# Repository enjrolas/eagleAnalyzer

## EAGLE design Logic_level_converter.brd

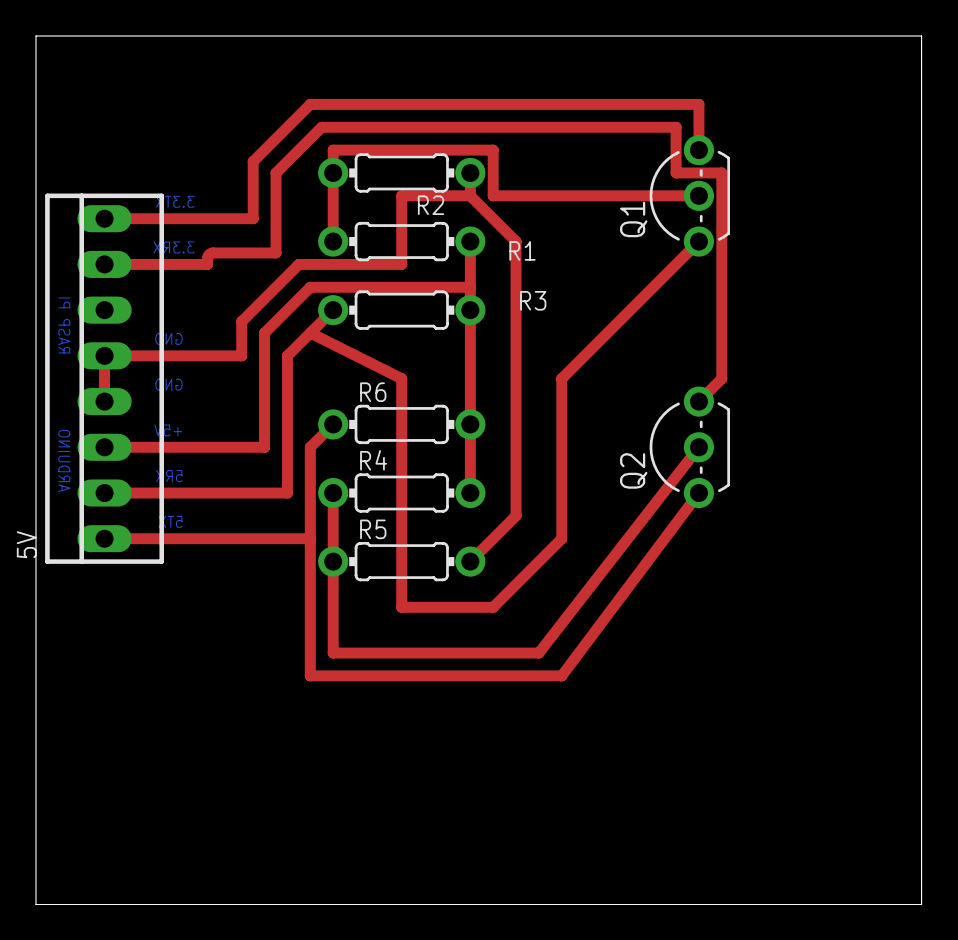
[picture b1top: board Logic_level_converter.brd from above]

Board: 2 copper layers, 49.2 x 48.2 mm, 9 parts (0 on the bottom side), 8 nets.

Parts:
5V: 22-23-2081
Q1, Q2: 2N7000; TO92-
R1, R4: 4.7k; 0204/7
R2, R3, R5, R6: 10k; 0204/7

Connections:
unnamed: 5V.4, 5V.5, R2.1, R5.2
S$1: Q1.2, R1.2, R2.2
S$2: 5V.8, Q1.3
S$3: 5V.2, Q1.1, R3.1
S$5: Q2.2, R4.1, R5.1
S$6: 5V.3, R1.1, R3.2, R4.2, R6.2
S$7: 5V.1, Q2.1, R6.1
S$8: 5V.7, Q2.3

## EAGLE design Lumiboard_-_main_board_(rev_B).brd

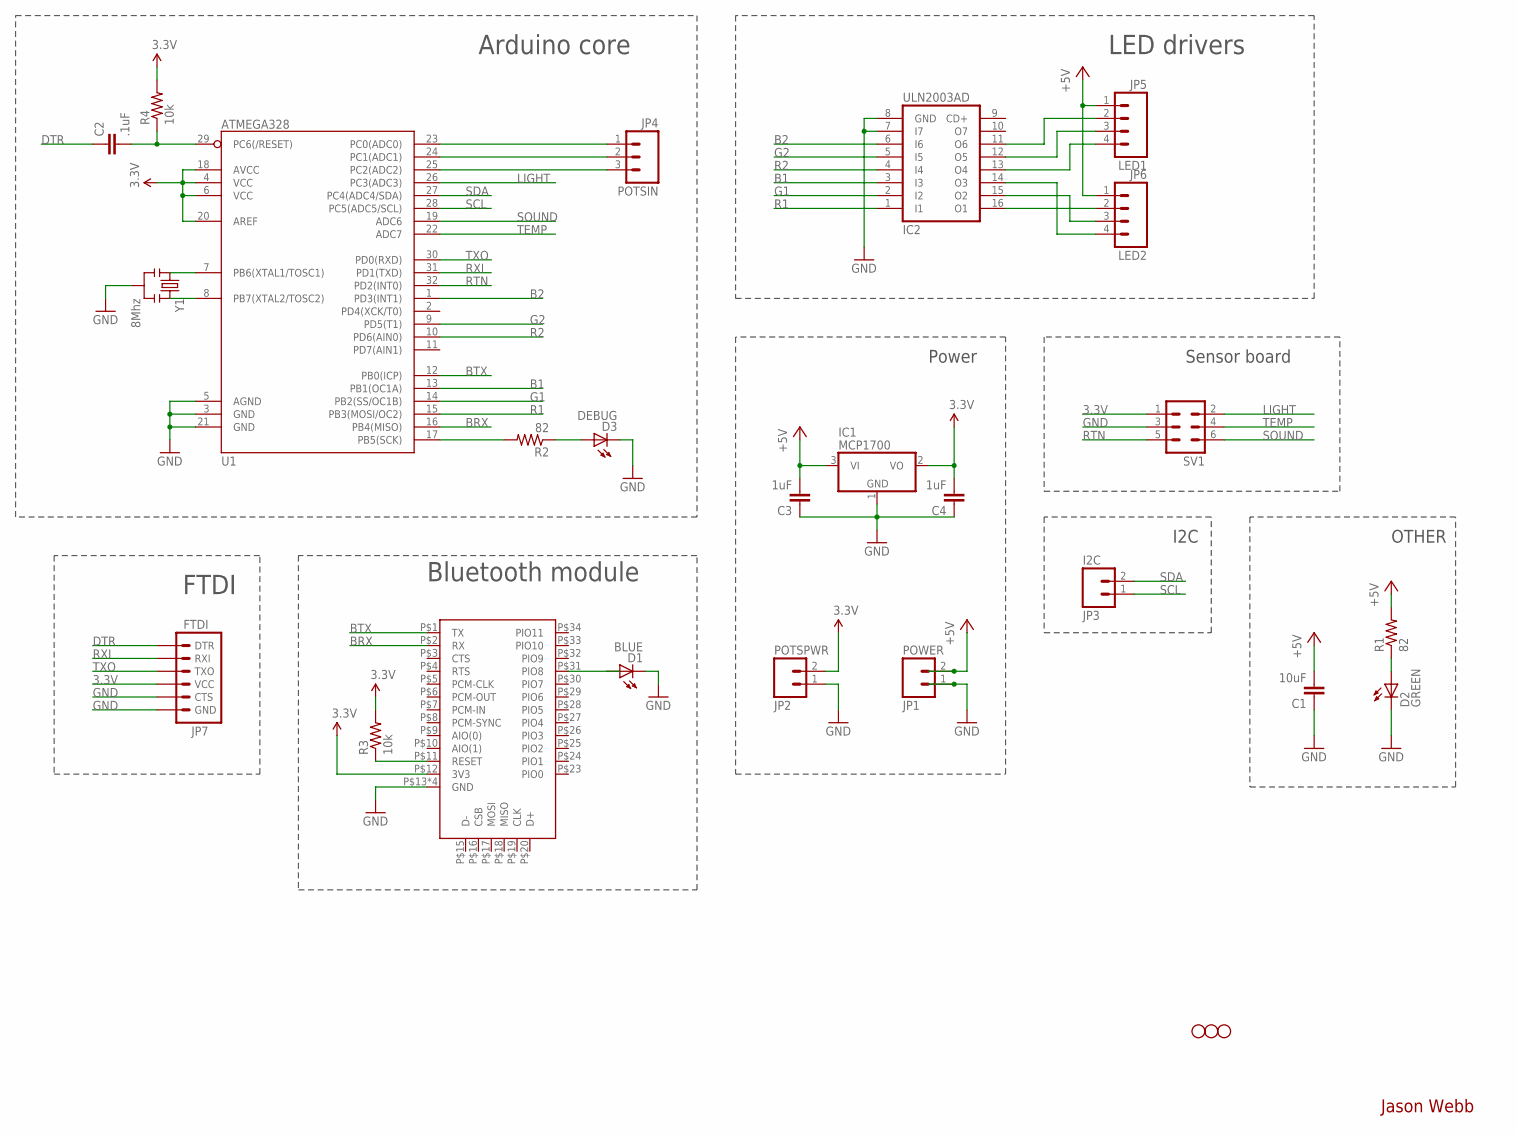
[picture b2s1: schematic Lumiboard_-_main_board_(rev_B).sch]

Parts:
C1: 10uF; 0805
C2: .1uF; 0805
C3, C4: 1uF; 0805
D1: BLUE; CHIPLED_0805
D2: GREEN; CHIPLED_0805
D3: DEBUG; CHIPLED_0805
I2C: JP3; 1X02
IC1: MCP1700; SOT23
IC2: ULN2003AD; SO16
JP2, JP4, JP5: STAND-OFFTIGHT; STAND-OFF-TIGHT
JP7: FTDI; 1X06_LOCK
LED1: JP5; 1X04
LED2: JP6; 1X04
POTSIN: JP4; 1X03
POTSPWR: JP2; 1X02
POWER: JP1; 1X02
R1, R2: 82; R0805
R3, R4: 10k; R0805
SV1: ML6
U1: ATMEGA328; TQFP32-08
U2: DX_BT_MODULE; DXBLUETOOTHMODULE
Y1: 8Mhz; RESONATOR-SMD

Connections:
3.3V: C4.2, IC1.2 (VO), JP7.4 (VCC), POTSPWR.2, R3.2, R4.2, SV1.1, U1.4 (VCC), U1.6 (VCC), U1.18 (AVCC), U1.20 (AREF), U2.P$12 (3V3)
+5V: C1.2, C3.2, IC1.3 (VI), LED1.1, LED2.1, POWER.2, R1.2
B1: IC2.3 (I3), U1.13 (PB1(OC1A))
B2: IC2.6 (I6), U1.1 (PD3(INT1))
BRX: U1.16 (PB4(MISO)), U2.P$2 (RX)
BTX: U1.12 (PB0(ICP)), U2.P$1 (TX)
DTR: C2.1, JP7.1 (DTR)
G1: IC2.2 (I2), U1.14 (PB2(SS/OC1B))
G2: IC2.5 (I5), U1.9 (PD5(T1))
GND: C1.1, C3.1, C4.1, D1.C, D2.C, D3.C, IC1.1 (GND), IC2.7 (I7), IC2.8 (GND), JP7.5 (CTS), JP7.6 (GND), POTSPWR.1, POWER.1, SV1.3, U1.3 (GND), U1.5 (AGND), U1.21 (GND), U2.P$13 (GND), U2.P$14 (GND), U2.P$21 (GND), U2.P$22 (GND), Y1.2
LIGHT: SV1.2, U1.26 (PC3(ADC3))
unnamed: IC2.16 (O1), LED2.2
unnamed: D1.A, U2.P$31 (PIO8)
unnamed: IC2.15 (O2), LED2.3
unnamed: R2.2, U1.17 (PB5(SCK))
unnamed: IC2.14 (O3), LED2.4
unnamed: U1.7 (PB6(XTAL1/TOSC1)), Y1.1
unnamed: U1.8 (PB7(XTAL2/TOSC2)), Y1.3
unnamed: D2.A, R1.1
unnamed: C2.2, R4.1, U1.29 (PC6(/RESET))
unnamed: R3.1, U2.P$11 (RESET)
unnamed: POTSIN.3, U1.25 (PC2(ADC2))
unnamed: D3.A, R2.1
unnamed: IC2.13 (O4), LED1.4
unnamed: IC2.12 (O5), LED1.3
unnamed: IC2.11 (O6), LED1.2
unnamed: POTSIN.2, U1.24 (PC1(ADC1))
unnamed: POTSIN.1, U1.23 (PC0(ADC0))
R1: IC2.1 (I1), U1.15 (PB3(MOSI/OC2))
R2: IC2.4 (I4), U1.10 (PD6(AIN0))
RTN: SV1.5, U1.32 (PD2(INT0))
RXI: JP7.2 (RXI), U1.31 (PD1(TXD))
SCL: I2C.1, U1.28 (PC5(ADC5/SCL))
SDA: I2C.2, U1.27 (PC4(ADC4/SDA))
SOUND: SV1.6, U1.19 (ADC6)
TEMP: SV1.4, U1.22 (ADC7)
TXO: JP7.3 (TXO), U1.30 (PD0(RXD))

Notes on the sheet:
Jason Webb
Arduino core
Bluetooth module
Sensor board
LED drivers
Power
FTDI
I2C
OTHER

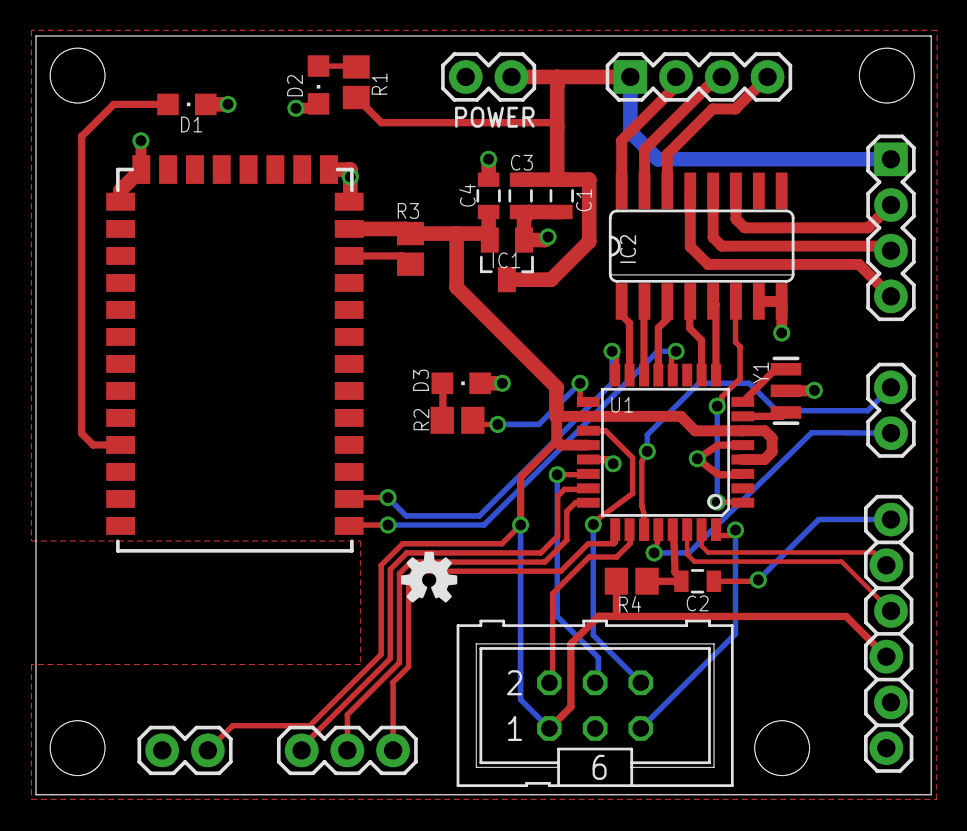
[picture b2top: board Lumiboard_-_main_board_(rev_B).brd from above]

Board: 2 copper layers, 49.7 x 42.2 mm, 29 parts (0 on the bottom side), 37 nets.

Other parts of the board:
JP3: STAND-OFFTIGHT; STAND-OFF-TIGHT
U$1: OSHW-LOGO-S

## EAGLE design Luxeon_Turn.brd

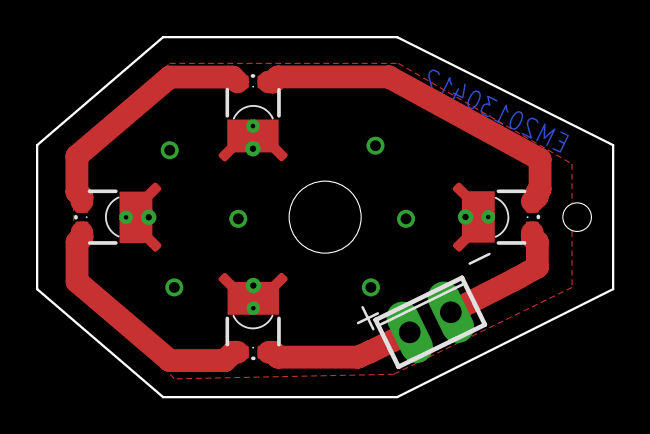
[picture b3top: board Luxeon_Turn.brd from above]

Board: 2 copper layers, 32.0 x 20.0 mm, 5 parts (0 on the bottom side), 6 nets.

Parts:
LED1, LED2, LED3, LED4: LUXEON_REBEL
X1: 2POL254

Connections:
unnamed: LED1.A, LED1.A@1, LED2.C, LED2.C@1
unnamed: LED2.A, LED2.A@1, LED3.C, LED3.C@1
unnamed: LED3.A, LED3.A@1, LED4.C, LED4.C@1
THERMAL: LED1.TH, LED1.TH@1, LED1.TH@2, LED1.TH@3, LED1.TH@4, LED2.TH, LED2.TH@1, LED2.TH@2, LED2.TH@3, LED2.TH@4, LED3.TH, LED3.TH@1, LED3.TH@2, LED3.TH@3, LED3.TH@4, LED4.TH, LED4.TH@1, LED4.TH@2, LED4.TH@3, LED4.TH@4
V+: LED4.A, LED4.A@1, X1.1
V-: LED1.C, LED1.C@1, X1.2

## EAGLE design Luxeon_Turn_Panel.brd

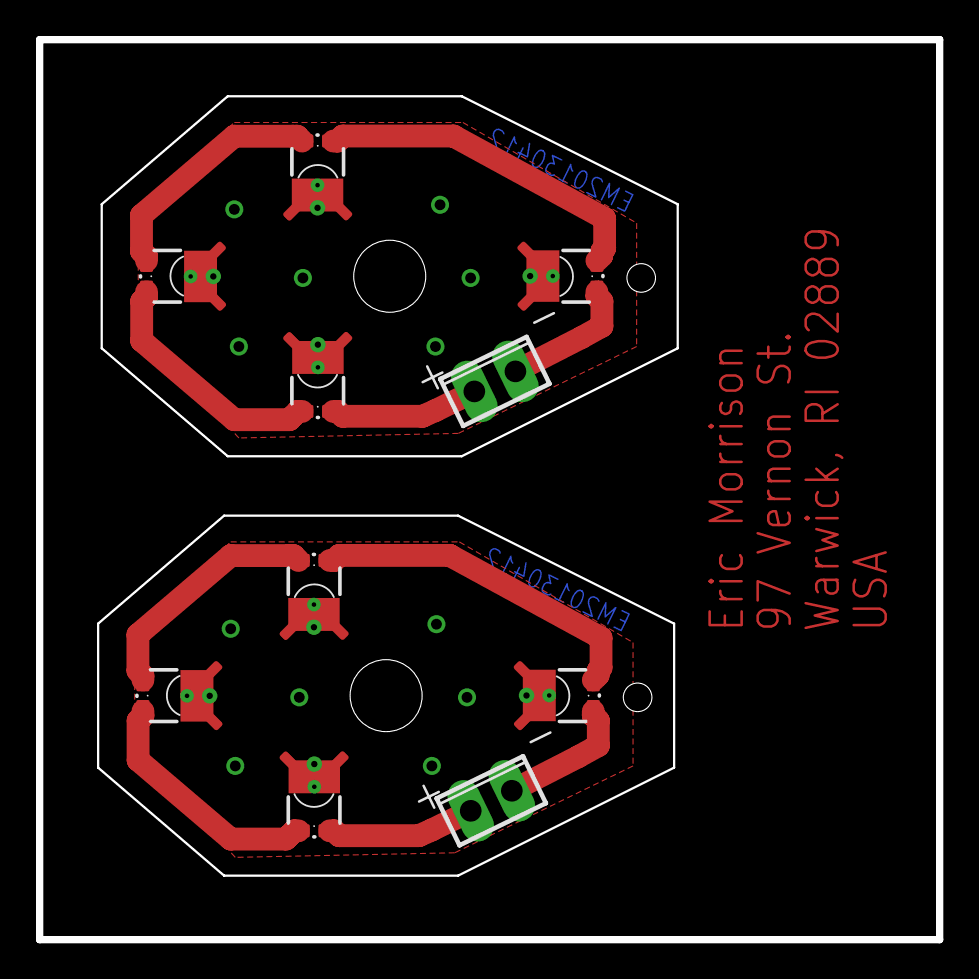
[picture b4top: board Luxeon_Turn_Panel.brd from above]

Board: 2 copper layers, 50.0 x 50.0 mm, 10 parts (0 on the bottom side), 12 nets.

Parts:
LED1, LED2, LED3, LED4, LED5, LED6, LED7, LED8: LUXEON_REBEL
X1, X2: 2POL254

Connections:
unnamed: LED5.A, LED5.A@1, LED6.C, LED6.C@1
unnamed: LED1.A, LED1.A@1, LED2.C, LED2.C@1
unnamed: LED2.A, LED2.A@1, LED3.C, LED3.C@1
unnamed: LED3.A, LED3.A@1, LED4.C, LED4.C@1
unnamed: LED6.A, LED6.A@1, LED7.C, LED7.C@1
unnamed: LED7.A, LED7.A@1, LED8.C, LED8.C@1
THERMAL: LED1.TH, LED1.TH@1, LED1.TH@2, LED1.TH@3, LED1.TH@4, LED2.TH, LED2.TH@1, LED2.TH@2, LED2.TH@3, LED2.TH@4, LED3.TH, LED3.TH@1, LED3.TH@2, LED3.TH@3, LED3.TH@4, LED4.TH, LED4.TH@1, LED4.TH@2, LED4.TH@3, LED4.TH@4
THERMAL1: LED5.TH, LED5.TH@1, LED5.TH@2, LED5.TH@3, LED5.TH@4, LED6.TH, LED6.TH@1, LED6.TH@2, LED6.TH@3, LED6.TH@4, LED7.TH, LED7.TH@1, LED7.TH@2, LED7.TH@3, LED7.TH@4, LED8.TH, LED8.TH@1, LED8.TH@2, LED8.TH@3, LED8.TH@4
V+: LED4.A, LED4.A@1, X1.1
V+1: LED8.A, LED8.A@1, X2.1
V-: LED1.C, LED1.C@1, X1.2
V-1: LED5.C, LED5.C@1, X2.2

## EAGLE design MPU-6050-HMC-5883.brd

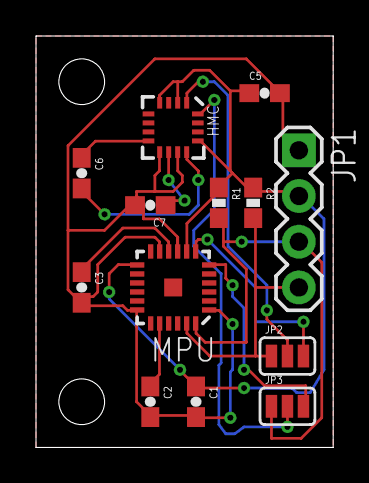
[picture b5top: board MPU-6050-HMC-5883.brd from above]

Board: 2 copper layers, 16.5 x 22.9 mm, 13 parts (0 on the bottom side), 13 nets.

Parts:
C1, C2, C3, C5, C6, C7: 0603-CAP
HMC: HMC5883LSMD; 16LPCC
JP1: 1X04
JP2, JP3: JUMPER-3SMD; SJ_3
MPU: MPU-6050; QFN-24
R1, R2: 0603-RES

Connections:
ACL: JP2.3, MPU.7
ADA: JP3.3, MPU.6
C1: C7.1, HMC.10
CPOUT: C2.1, MPU.20
GND: C1.2, C2.2, C3.2, C5.2, C7.2, HMC.9, HMC.11, JP1.1, MPU.1, MPU.9, MPU.11, MPU.18
REGOUT: C3.1, MPU.10
SCL: JP1.4, JP2.1, MPU.23, R2.2
SCLHMC: HMC.1, JP2.2
SDA: JP1.3, JP3.1, MPU.24, R1.2
SDAHMC: HMC.16, JP3.2
SETC: C6.2, HMC.12
SETP: C6.1, HMC.8
VCC: C1.1, C5.1, HMC.2, HMC.4, HMC.13, JP1.2, MPU.8, MPU.13, R1.1, R2.1

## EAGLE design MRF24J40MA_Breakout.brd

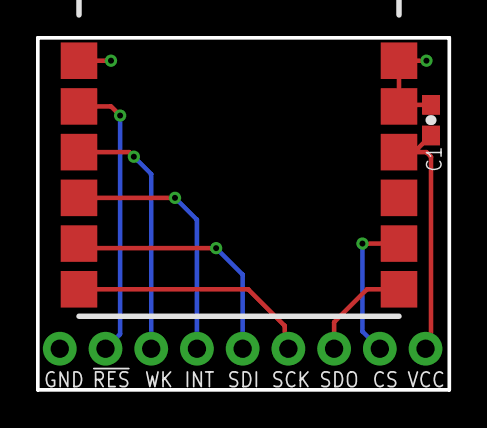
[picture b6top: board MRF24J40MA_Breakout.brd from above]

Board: 2 copper layers, 22.9 x 19.6 mm, 3 parts (1 on the bottom side), 9 nets.

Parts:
C1: 0603-CAP
JP1: M09; 1X09
U1: MRF24J40MA

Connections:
!CS: JP1.8, U1.8
!RESET: JP1.2, U1.2
GND: C1.2, JP1.1, U1.1, U1.11, U1.12
INT: JP1.4, U1.4
SCK: JP1.6, U1.6
SDI: JP1.5, U1.5
SDO: JP1.7, U1.7
VCC: C1.1, JP1.9, U1.10
WAKE: JP1.3, U1.3

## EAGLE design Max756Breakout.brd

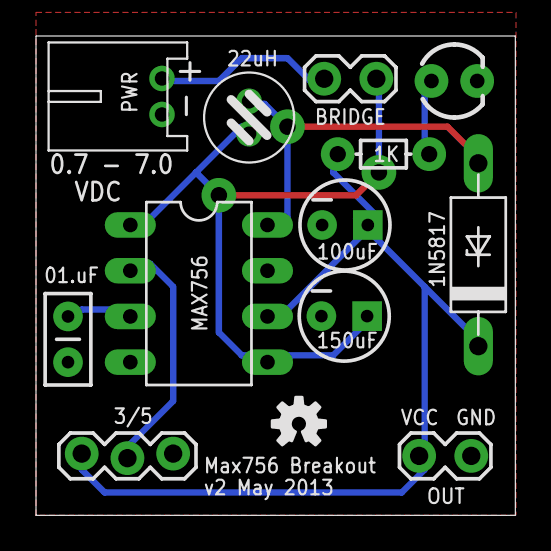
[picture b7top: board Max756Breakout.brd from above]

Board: 2 copper layers, 26.6 x 26.6 mm, 14 parts (0 on the bottom side), 8 nets.

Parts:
3/5: 1X03_LOCK
BRIDGE: 1X02_LOCK
C1: 100uF; CPOL-RADIAL-10UF-25V
C2: 150uF; CPOL-RADIAL-10UF-25V
C3: 01.uF; CAP-PTH-SMALL2
D1: 1N5817; F126Z12
FRAME1: FRAME-LETTER; CREATIVE_COMMONS
L1: 22uH; 82114R
LED1: LED3MM
MAX756: MAX756CPA; DIL08
OUT: 1X02_LOCK
PWR: 0.7 - 7.0VDC; JST-PH-2-THM-RA
R1: 1K; AXIAL-0.2
U$1: OSHW-LOGO-S

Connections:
3/5: 3/5.2, MAX756.2
GND: 3/5.3, C1.2, C2.2, C3.2, LED1.K, MAX756.7, OUT.2, PWR.2
L1: D1.A, L1.1, MAX756.8
unnamed: BRIDGE.2, PWR.1
unnamed: LED1.A, R1.P$2
REF: C3.1, MAX756.3
VCC: 3/5.1, C1.1, D1.C, MAX756.6, OUT.1, R1.P$1
VIN: BRIDGE.1, C2.1, L1.2, MAX756.1, MAX756.5

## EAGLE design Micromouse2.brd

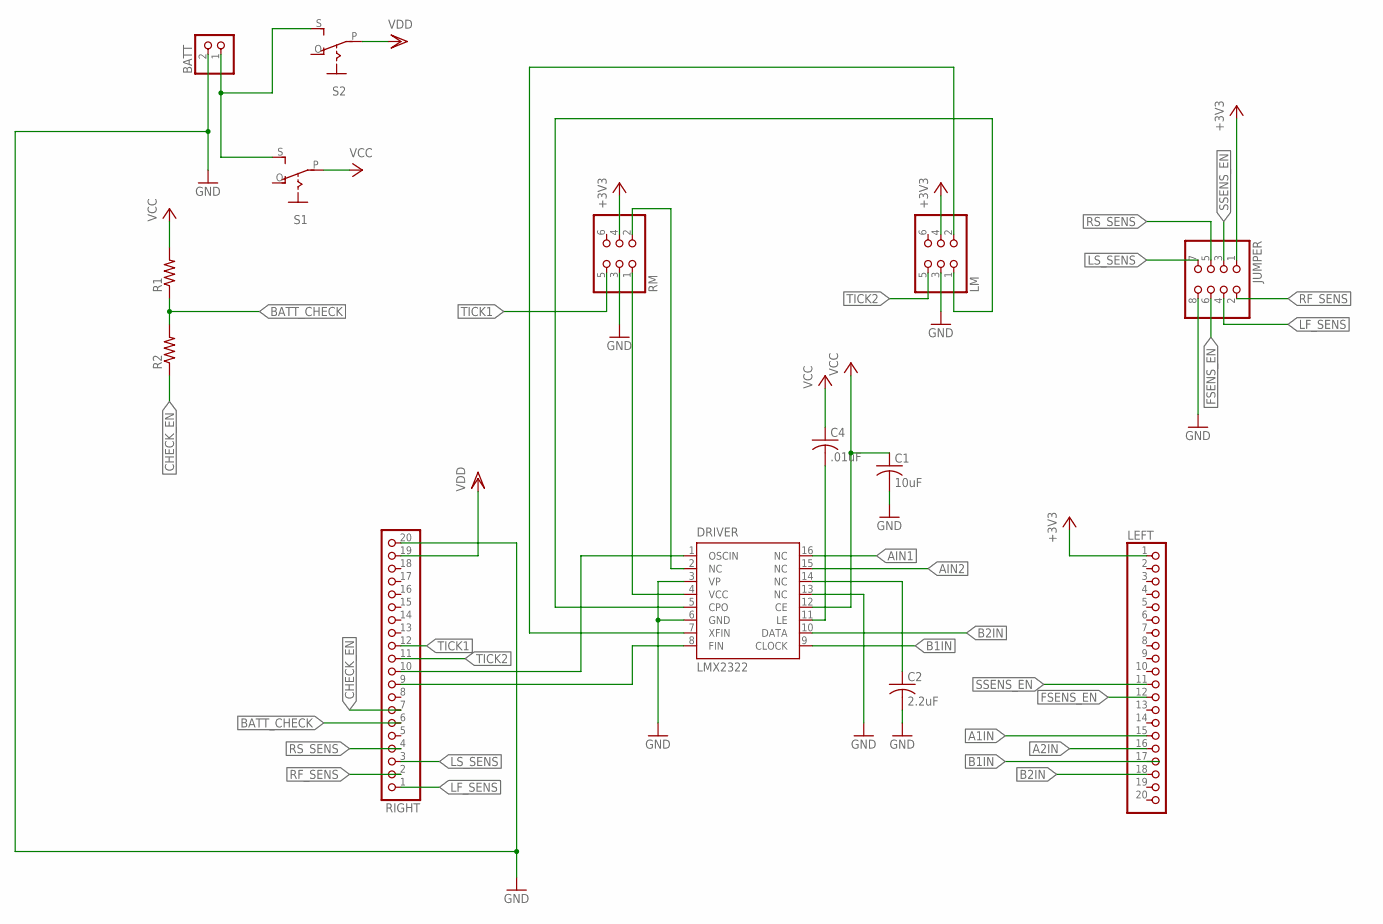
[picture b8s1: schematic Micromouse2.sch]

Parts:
BATT: JST_2PIN-THM; JST-PH-2-THM
C1: 10uF; C0805
C2: 2.2uF; C0805
C4: .01uF; C0805
DRIVER: LMX2322; TSSOP16
JUMPER: PINHD-2X4; 2X04
LEFT: PINHD-1X20; 1X20
LM: PINHD-2X3; 2X03
R1, R2: R-US_R0805; R0805
RIGHT: PINHD-1X20; 1X20
RM: PINHD-2X3; 2X03
S1, S2: EG1218S; EG1218

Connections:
+3V3: JUMPER.1, LEFT.1, LM.4, RM.4
A1IN: LEFT.15
A2IN: LEFT.16
AIN1: DRIVER.16 (NC)
AIN2: DRIVER.15 (NC)
B1IN: DRIVER.9 (CLOCK)
B2IN: DRIVER.10 (DATA), LEFT.18
BATT_CHECK: R1.1, R2.2, RIGHT.6
CHECK_EN: R2.1, RIGHT.7
FSENS_EN: JUMPER.6, LEFT.12
GND: BATT.2 (1), C1.2, C2.2, DRIVER.3 (VP), DRIVER.6 (GND), DRIVER.13 (NC), JUMPER.8, LM.3, RIGHT.20, RM.3
LF_SENS: JUMPER.4, RIGHT.1
LS_SENS: JUMPER.7, RIGHT.3
unnamed: DRIVER.2 (NC), RM.2
unnamed: C2.1, DRIVER.14 (NC)
unnamed: DRIVER.4 (VCC), RM.1
unnamed: C4.2, DRIVER.11 (LE)
unnamed: DRIVER.7 (XFIN), LM.2
unnamed: DRIVER.5 (CPO), LM.1
unnamed: BATT.1 (2), S1.S, S2.S
unnamed: DRIVER.8 (FIN), RIGHT.9
unnamed: DRIVER.1 (OSCIN), RIGHT.10
RF_SENS: JUMPER.2, RIGHT.2
RS_SENS: JUMPER.5, RIGHT.4
SSENS_EN: JUMPER.3, LEFT.11
TICK1: RIGHT.12, RM.5
TICK2: LM.5, RIGHT.11
VCC: C1.1, C4.1, DRIVER.12 (CE), R1.2, S1.P
VDD: RIGHT.19, S2.P

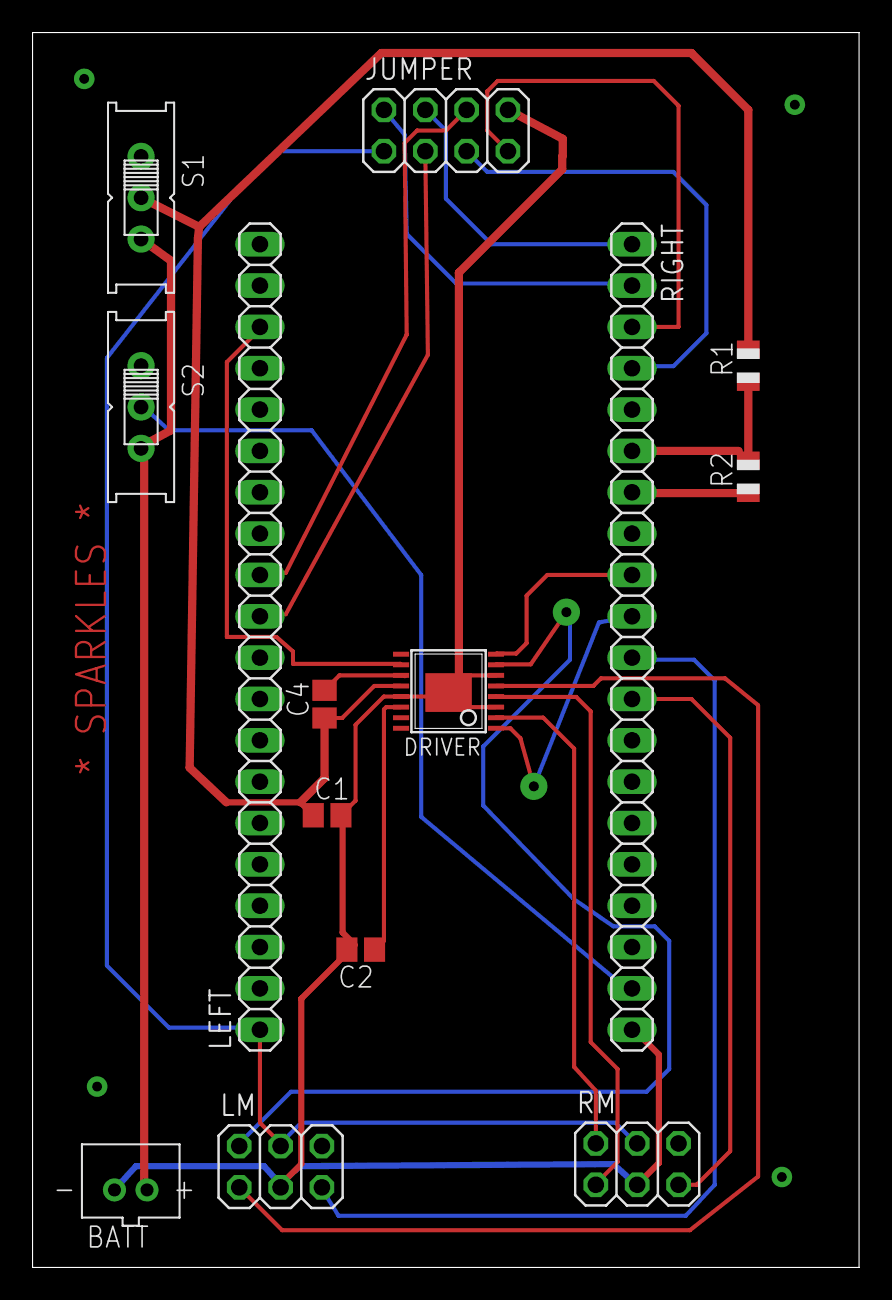
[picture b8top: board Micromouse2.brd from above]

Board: 2 copper layers, 50.8 x 75.9 mm, 14 parts (0 on the bottom side), 24 nets.

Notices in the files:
parts and their libraries:
SparkFun-Connectors: Licensing: CC v3.0 Share-Alike You are welcome to use this library for commercial purposes.
SparkFun-Aesthetics: Released under the Creative Commons Attribution Share-Alike 3.0 License
SparkFun-Aesthetics: http://creativecommons.org/licenses/by-sa/3.0
